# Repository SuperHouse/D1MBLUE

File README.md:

Bluetooth Shield for the WeMos D1 Mini
======================================

Copyright 2016 SuperHouse Automation Pty Ltd  
SuperHouse site:  www.superhouse.tv  
SuperHouse email: info@superhouse.tv  

A Bluetooth serial shield for the [WeMos D1 Mini][1] 
and other compatible boards based on the same header format.

Features:

 * HC-05 master/slave Bluetooth module.
 * Jumper to link Bluetooth reset to D1 Mini reset.
 * Jumper to place Bluetooth module into command mode for reflashing, etc.

More information is available at:

  http://www.superhouse.tv/d1mblue

INSTALLATION
------------
The design is saved as an EAGLE project. EAGLE PCB design software is
available from www.cadsoftusa.com free for non-commercial use. To use
this project download it and place the directory containing these files
into the "eagle" directory on your computer.

DISTRIBUTION
------------
The specific terms of distribution of this project are governed by the
license referenced below.

LICENSE
-------
Licensed under the TAPR Open Hardware License (www.tapr.org/OHL).
The "license" folder within this repository also contains a copy of
this license in plain text format.

[1]: http://www.wemos.cc/wiki/doku.php?id=en:d1_mini

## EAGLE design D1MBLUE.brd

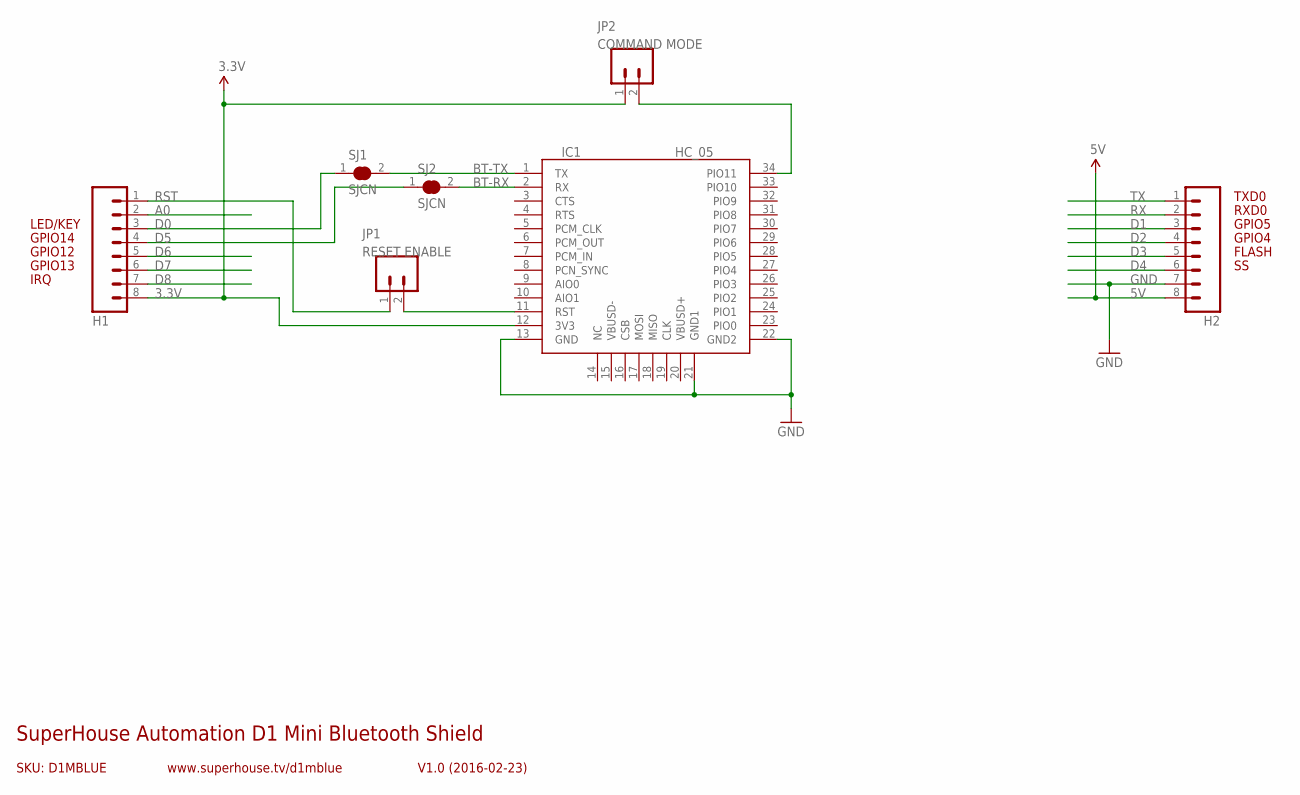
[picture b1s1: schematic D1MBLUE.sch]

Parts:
H1, H2: M08; 1X08
IC1: HC_05; BLUETOOTH_SMD
JP1: RESET ENABLE; 1X02
JP2: COMMAND MODE; 1X02
SJ1, SJ2: SJCN; SJC

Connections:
3.3V: H1.8, IC1.12 (3V3), JP2.1
5V: H2.8
A0: H1.2
BT-RX: IC1.2 (RX), SJ2.2
BT-TX: IC1.1 (TX), SJ1.2
D0: H1.3, SJ1.1
D1: H2.3
D2: H2.4
D3: H2.5
D4: H2.6
D5: H1.4, SJ2.1
D6: H1.5
D7: H1.6
D8: H1.7
GND: H2.7, IC1.13 (GND), IC1.21 (GND1), IC1.22 (GND2)
unnamed: IC1.11 (RST), JP1.2
unnamed: IC1.34 (PIO11), JP2.2
RST: H1.1, JP1.1
RX: H2.2
TX: H2.1

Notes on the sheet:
FLASH
GPIO12
GPIO4
GPIO5
RXD0
TXD0
GPIO13
GPIO14
IRQ
LED/KEY
SKU: D1MBLUE
SuperHouse Automation D1 Mini Bluetooth Shield
V1.0 (2016-02-23)
www.superhouse.tv/d1mblue

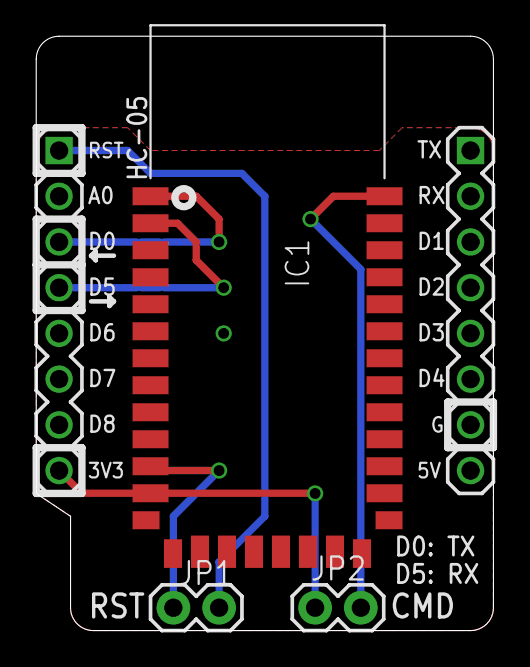
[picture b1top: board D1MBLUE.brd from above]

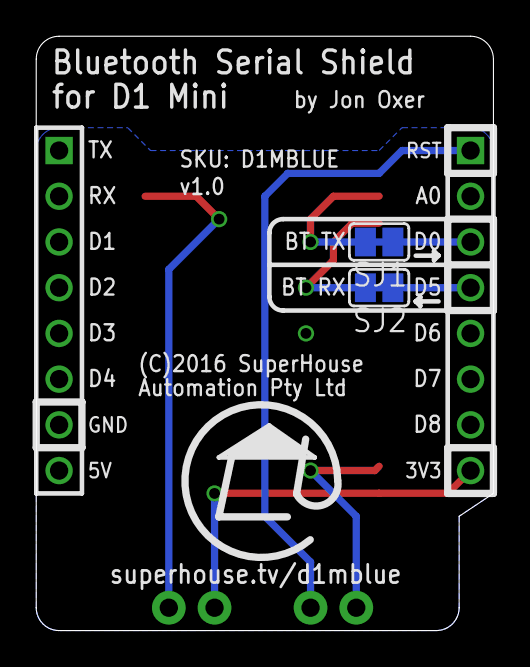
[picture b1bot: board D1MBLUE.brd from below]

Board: 2 copper layers, 25.4 x 33.0 mm, 7 parts (2 on the bottom side), 9 nets.

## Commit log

2016-02-26 Initial import
2016-02-26 Added license and images, and updated README
2016-02-26 Clarified description
2016-03-07 Improved silkscreen and updated preview images

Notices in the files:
D1MBLUE.brd:
(C)2016 SuperHouse
parts and their libraries:
freetronics-original: Licensing: CC v3.0 Share-Alike You are welcome to use this library for commercial purposes.
